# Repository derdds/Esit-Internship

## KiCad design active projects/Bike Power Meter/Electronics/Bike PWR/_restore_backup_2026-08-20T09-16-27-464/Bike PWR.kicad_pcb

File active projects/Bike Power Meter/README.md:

# Bike Power Meter

## Project Description
Add your project description here.

## Status
- Active/In Progress/Completed

## Key Files
- List important files here

## Notes
- Add any relevant notes

## Links
- Add links to documentation, repos, etc.

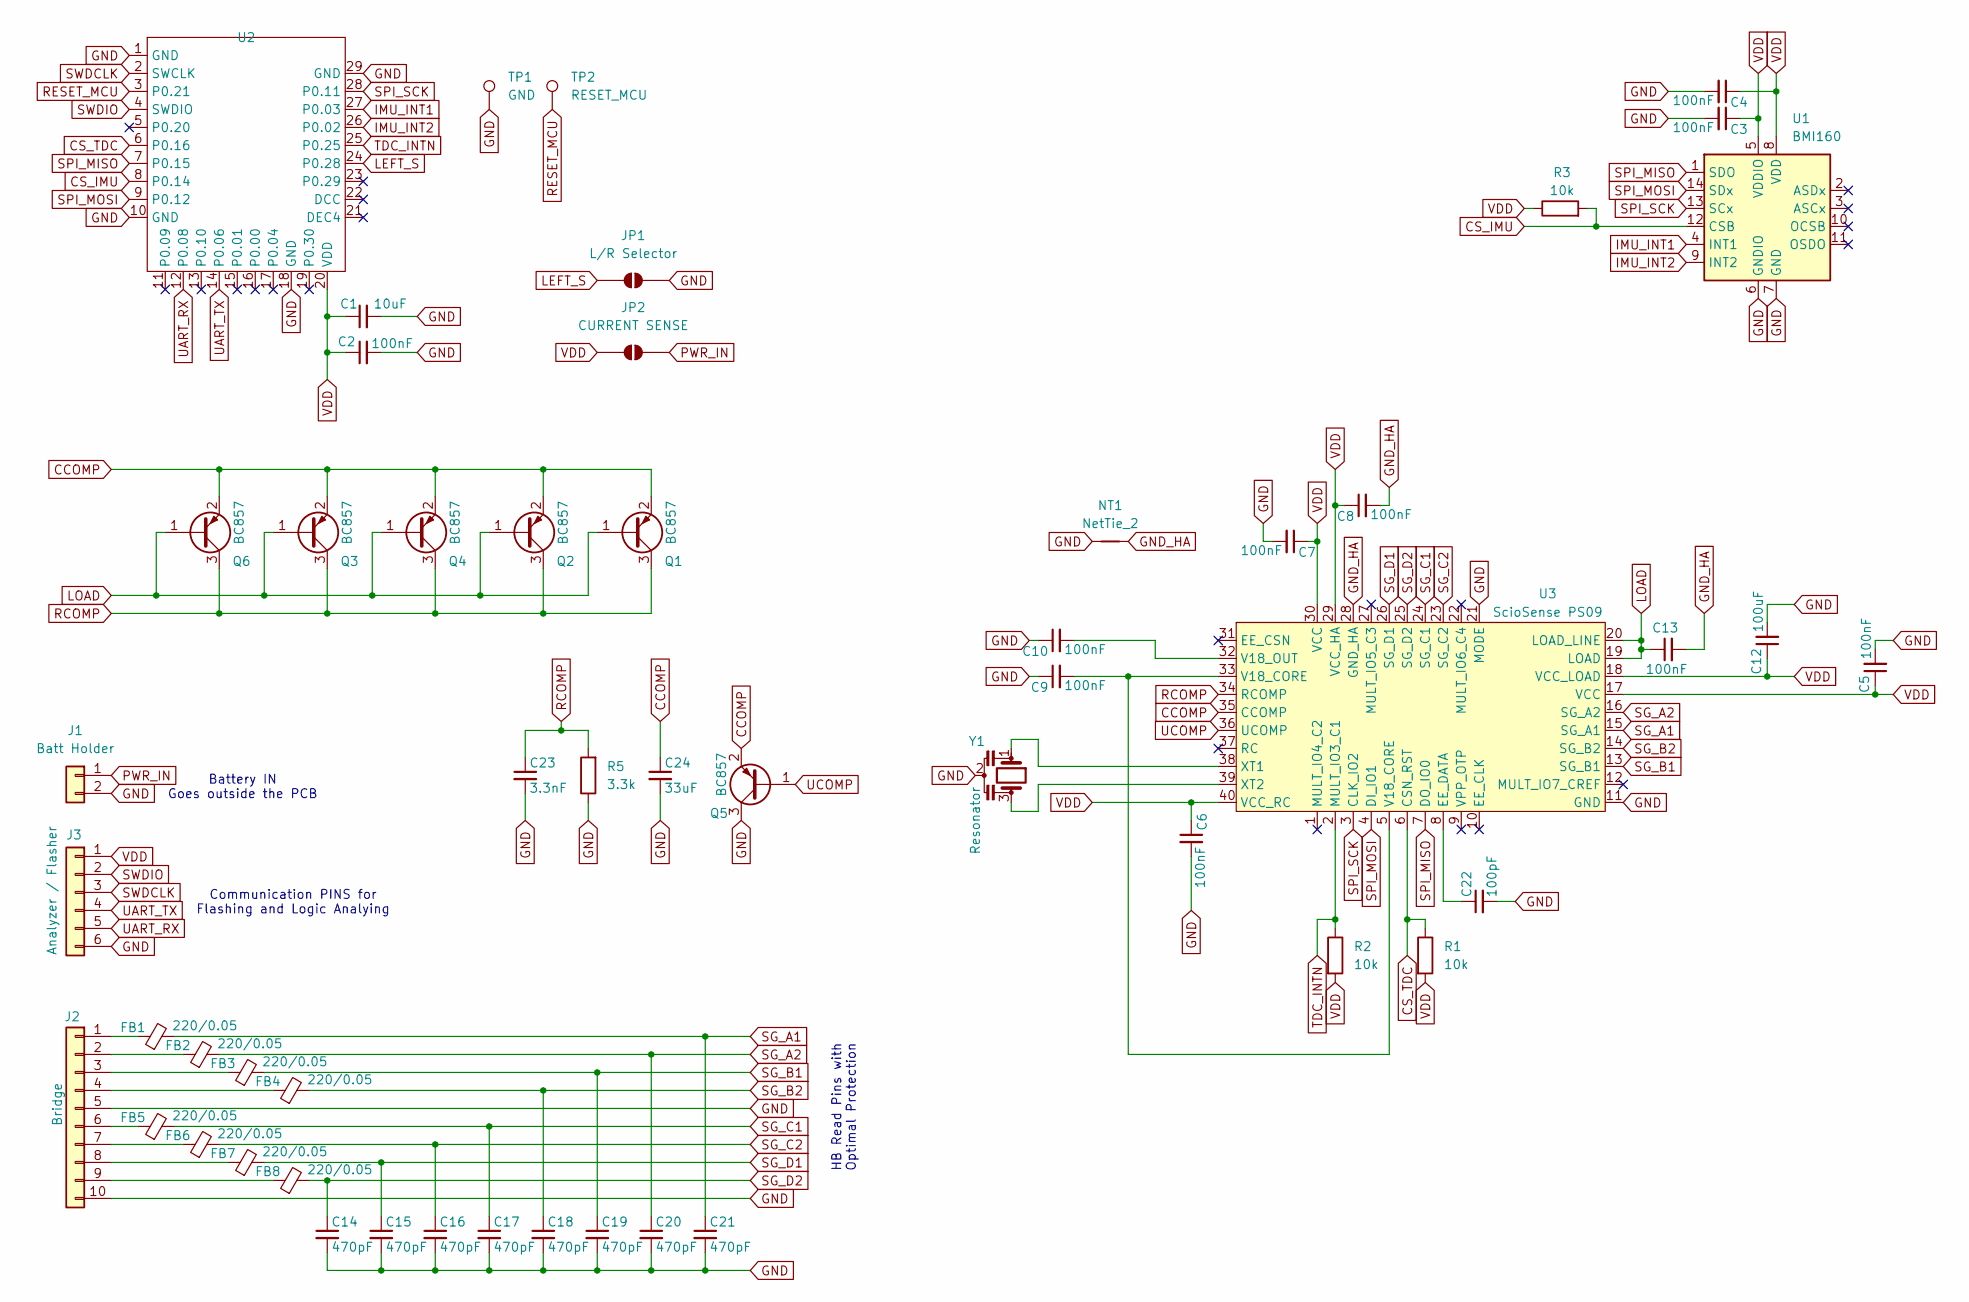
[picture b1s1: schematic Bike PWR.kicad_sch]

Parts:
C1: 10uF; C_0201_0603Metric_Pad0.64x0.40mm_HandSolder
C2, C3, C4, C5, C6, C7, C8, C9, C10, C13: 100nF; C_0201_0603Metric_Pad0.64x0.40mm_HandSolder
C12: 100uF; C_0201_0603Metric_Pad0.64x0.40mm_HandSolder
C14, C15, C16, C17, C18, C19, C20, C21: 470pF; C_0201_0603Metric_Pad0.64x0.40mm_HandSolder
C22: 100pF; C_0201_0603Metric_Pad0.64x0.40mm_HandSolder
C23: 3.3nF; C_0201_0603Metric_Pad0.64x0.40mm_HandSolder
C24: 33uF; C_0201_0603Metric_Pad0.64x0.40mm_HandSolder
FB1, FB2, FB3, FB4, FB5, FB6, FB7, FB8: 220/0.05; L_0201_0603Metric_Pad0.64x0.40mm_HandSolder
J1: Batt Holder; PWR Pins (2x2.54mm)
J2: Bridge; AFE SG (10x2.54mm)
J3: Analyzer / Flasher; UART Pins (6x2.54mm)
JP1: L/R Selector; SolderJumper-2_P1.3mm_Open_RoundedPad1.0x1.5mm
JP2: CURRENT SENSE; SolderJumper-2_P1.3mm_Open_RoundedPad1.0x1.5mm
NT1: NetTie_2; NetTie-2_SMD_Pad0.5mm
Q1, Q2, Q3, Q4, Q5, Q6: BC857; SOT-23
R1, R2, R3: 10k; R_0201_0603Metric_Pad0.64x0.40mm_HandSolder
R5: 3.3k; R_0201_0603Metric_Pad0.64x0.40mm_HandSolder
TP1: GND; TestPoint_Pad_D1.0mm
TP2: RESET_MCU; TestPoint_Pad_D1.0mm
U1: BMI160; Bosch_LGA-14_3x2.5mm_P0.5mm
U2: MDBT42V-512KV2
U3: ScioSense PS09; QFN-40-1EP_6x6mm_P0.5mm_EP4.6x4.6mm
Y1: Resonator; OSC_CSTCR4M00G53-R0

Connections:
CCOMP: C24.1, Q1.2 (E), Q2.2 (E), Q3.2 (E), Q4.2 (E), Q5.2 (E), Q6.2 (E), U3.35 (CCOMP)
CS_IMU: R3.2, U1.12 (CSB), U2.8 (P0.14)
CS_TDC: R1.1, U2.6 (P0.20), U3.6 (CSN_RST)
GND: C1.2, C2.2, C3.2, C4.2, C5.2, C6.2, C7.2, C9.1, C10.1, C12.2, C14.2, C15.2, C16.2, C17.2, C18.2, C19.2, C20.2, C21.2, C22.2, C23.2, C24.2, J1.2, J2.5, J2.10, J3.6, JP1.2 (B), NT1.1, Q5.3 (C), R5.1, TP1.1 (1_1), U1.6 (GNDIO), U1.7 (GND), U2.1 (GND), U2.10 (GND), U2.18 (GND), U2.29 (GND), U3.11 (GND), U3.21 (MODE), Y1.2; also elsewhere on the board
GND_HA: C8.2, C13.2, NT1.2, U3.28 (GND_HA)
IMU_INT1: U1.4 (INT1), U2.27 (P0.03)
IMU_INT2: U1.9 (INT2), U2.26 (P0.02)
LEFT_S: JP1.1 (A), U2.24 (P0.28); also elsewhere on the board
LOAD: C13.1, Q1.1 (B), Q2.1 (B), Q3.1 (B), Q4.1 (B), Q6.1 (B), U3.19 (LOAD), U3.20 (LOAD_LINE)
unnamed: C9.2, U3.5 (V18_CORE), U3.33 (V18_CORE)
unnamed: FB1.1, J2.1
unnamed: FB2.1, J2.2
unnamed: FB3.1, J2.3
unnamed: FB4.1, J2.4
unnamed: FB5.1, J2.6
unnamed: FB6.1, J2.7
unnamed: FB7.1, J2.8
unnamed: FB8.1, J2.9
unnamed: C22.1, U3.8 (EE_DATA)
unnamed: C10.2, U3.32 (V18_OUT)
unnamed: U3.38 (XT1), Y1.1
unnamed: U3.39 (XT2), Y1.3
PWR_IN: J1.1, JP2.2 (B); also elsewhere on the board
RCOMP: C23.1, Q1.3 (C), Q2.3 (C), Q3.3 (C), Q4.3 (C), Q6.3 (C), R5.2, U3.34 (RCOMP)
RESET_MCU: TP2.1 (1_1), U2.3 (P0.21)
SG_A1: C21.1, FB1.2, U3.15 (SG_A1)
SG_A2: C20.1, FB2.2, U3.16 (SG_A2)
SG_B1: C19.1, FB3.2, U3.13 (SG_B1)
SG_B2: C18.1, FB4.2, U3.14 (SG_B2)
SG_C1: C17.1, FB5.2, U3.24 (SG_C1)
SG_C2: C16.1, FB6.2, U3.23 (SG_C2)
SG_D1: C15.1, FB7.2, U3.26 (SG_D1)
SG_D2: C14.1, FB8.2, U3.25 (SG_D2)
SPI_MISO: U1.1 (SDO), U2.7 (P0.15), U3.7 (DO_IO0)
SPI_MOSI: U1.14 (SDx), U2.9 (P0.12), U3.4 (DI_IO1)
SPI_SCK: U1.13 (SCx), U2.28 (P0.11), U3.3 (CLK_IO2)
SWDCLK: J3.3, U2.2 (SWCLK)
SWDIO: J3.2, U2.4 (SWDIO)
TDC_INTN: R2.1, U2.25 (P0.25), U3.2 (MULT_IO3_C1)
UART_RX: J3.5, U2.12 (P0.08)
UART_TX: J3.4, U2.14 (P0.06)
UCOMP: Q5.1 (B), U3.36 (UCOMP)
VDD: C1.1, C2.1, C3.1, C4.1, C5.1, C6.1, C7.1, C8.1, C12.1, J3.1, JP2.1 (A), R1.2, R2.2, R3.1, U1.5 (VDDIO), U1.8 (VDD), U2.20 (VDD), U3.17 (VCC), U3.18 (VCC_LOAD), U3.29 (VCC_HA), U3.30 (VCC), U3.40 (VCC_RC); also elsewhere on the board

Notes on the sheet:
HB Read Pins with Optimal Protection
Communication PINS for Flashing and Logic Analying
Battery IN Goes outside the PCB

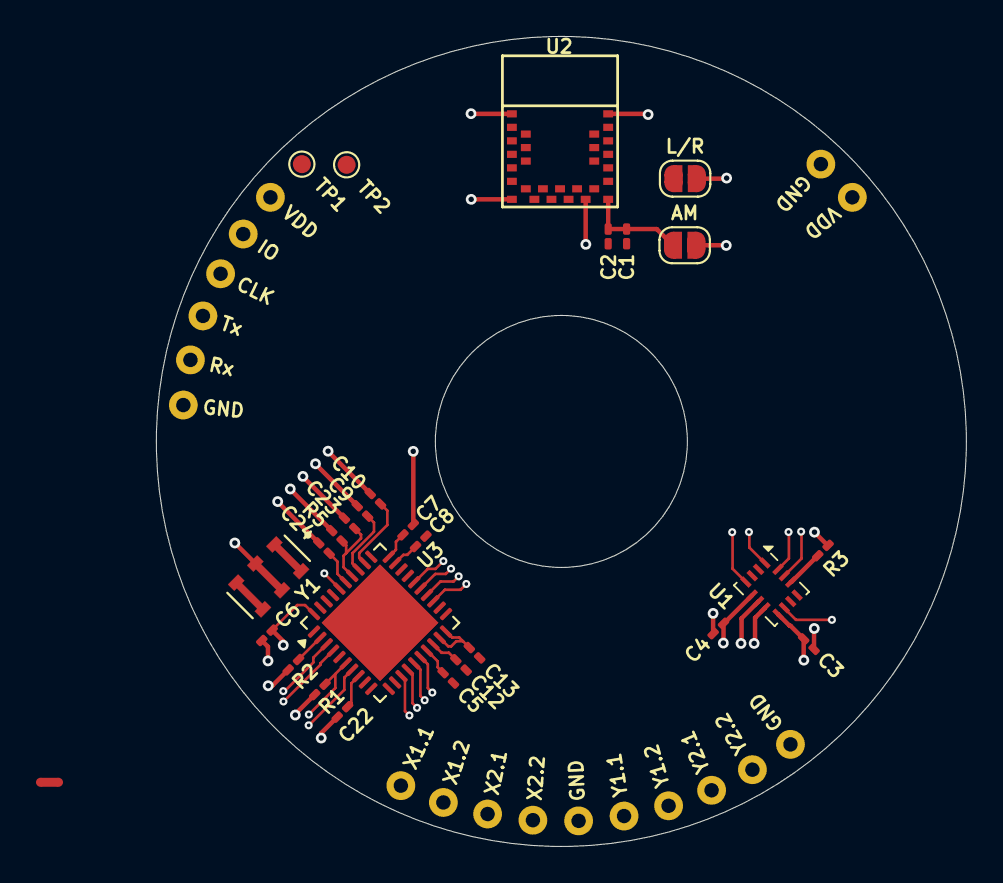
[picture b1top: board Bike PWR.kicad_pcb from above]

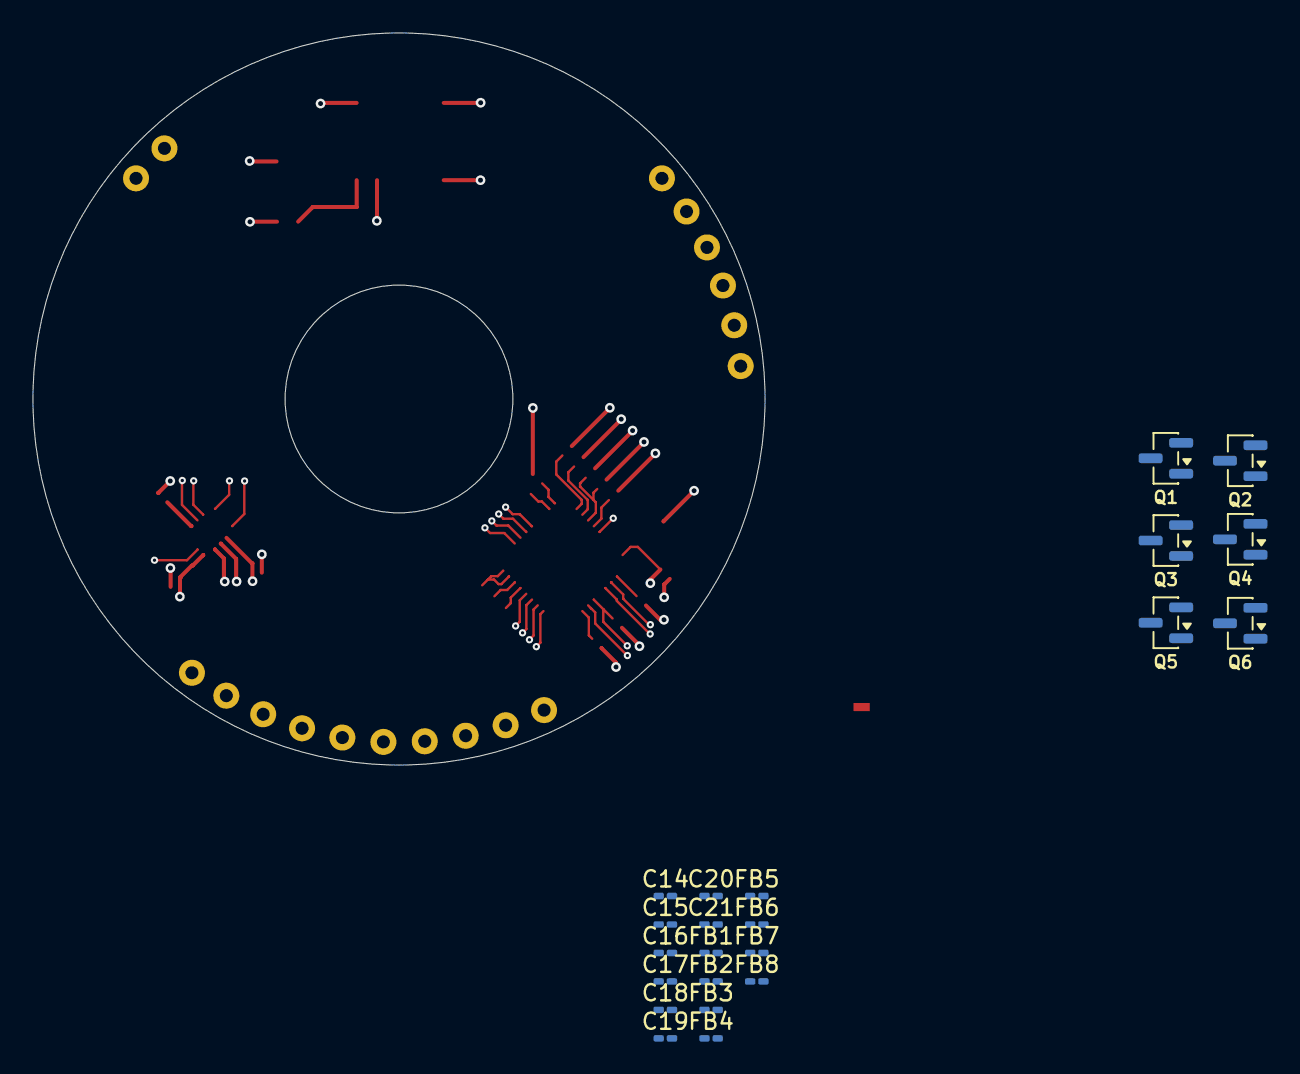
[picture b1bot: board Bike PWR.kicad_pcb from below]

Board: 4 copper layers, 45.0 x 45.0 mm, 53 parts (22 on the bottom side), 43 nets.

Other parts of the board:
AM: CURRENT SENSE; SolderJumper-2_P1.3mm_Open_RoundedPad1.0x1.5mm
L/R: L/R Selector; SolderJumper-2_P1.3mm_Open_RoundedPad1.0x1.5mm

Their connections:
GND: L/R.2 (B); also elsewhere on the board
LEFT_S: L/R.1 (A); also elsewhere on the board
PWR_IN: AM.2 (B); also elsewhere on the board
VDD: AM.1 (A); also elsewhere on the board

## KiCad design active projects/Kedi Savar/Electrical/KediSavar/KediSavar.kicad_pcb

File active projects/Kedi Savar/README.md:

# Kedi Savar

## Project Description
Add your project description here.

## Status
- Active/In Progress/Completed

## Key Files
- List important files here

## Notes
- Add any relevant notes

## Links
- Add links to documentation, repos, etc.

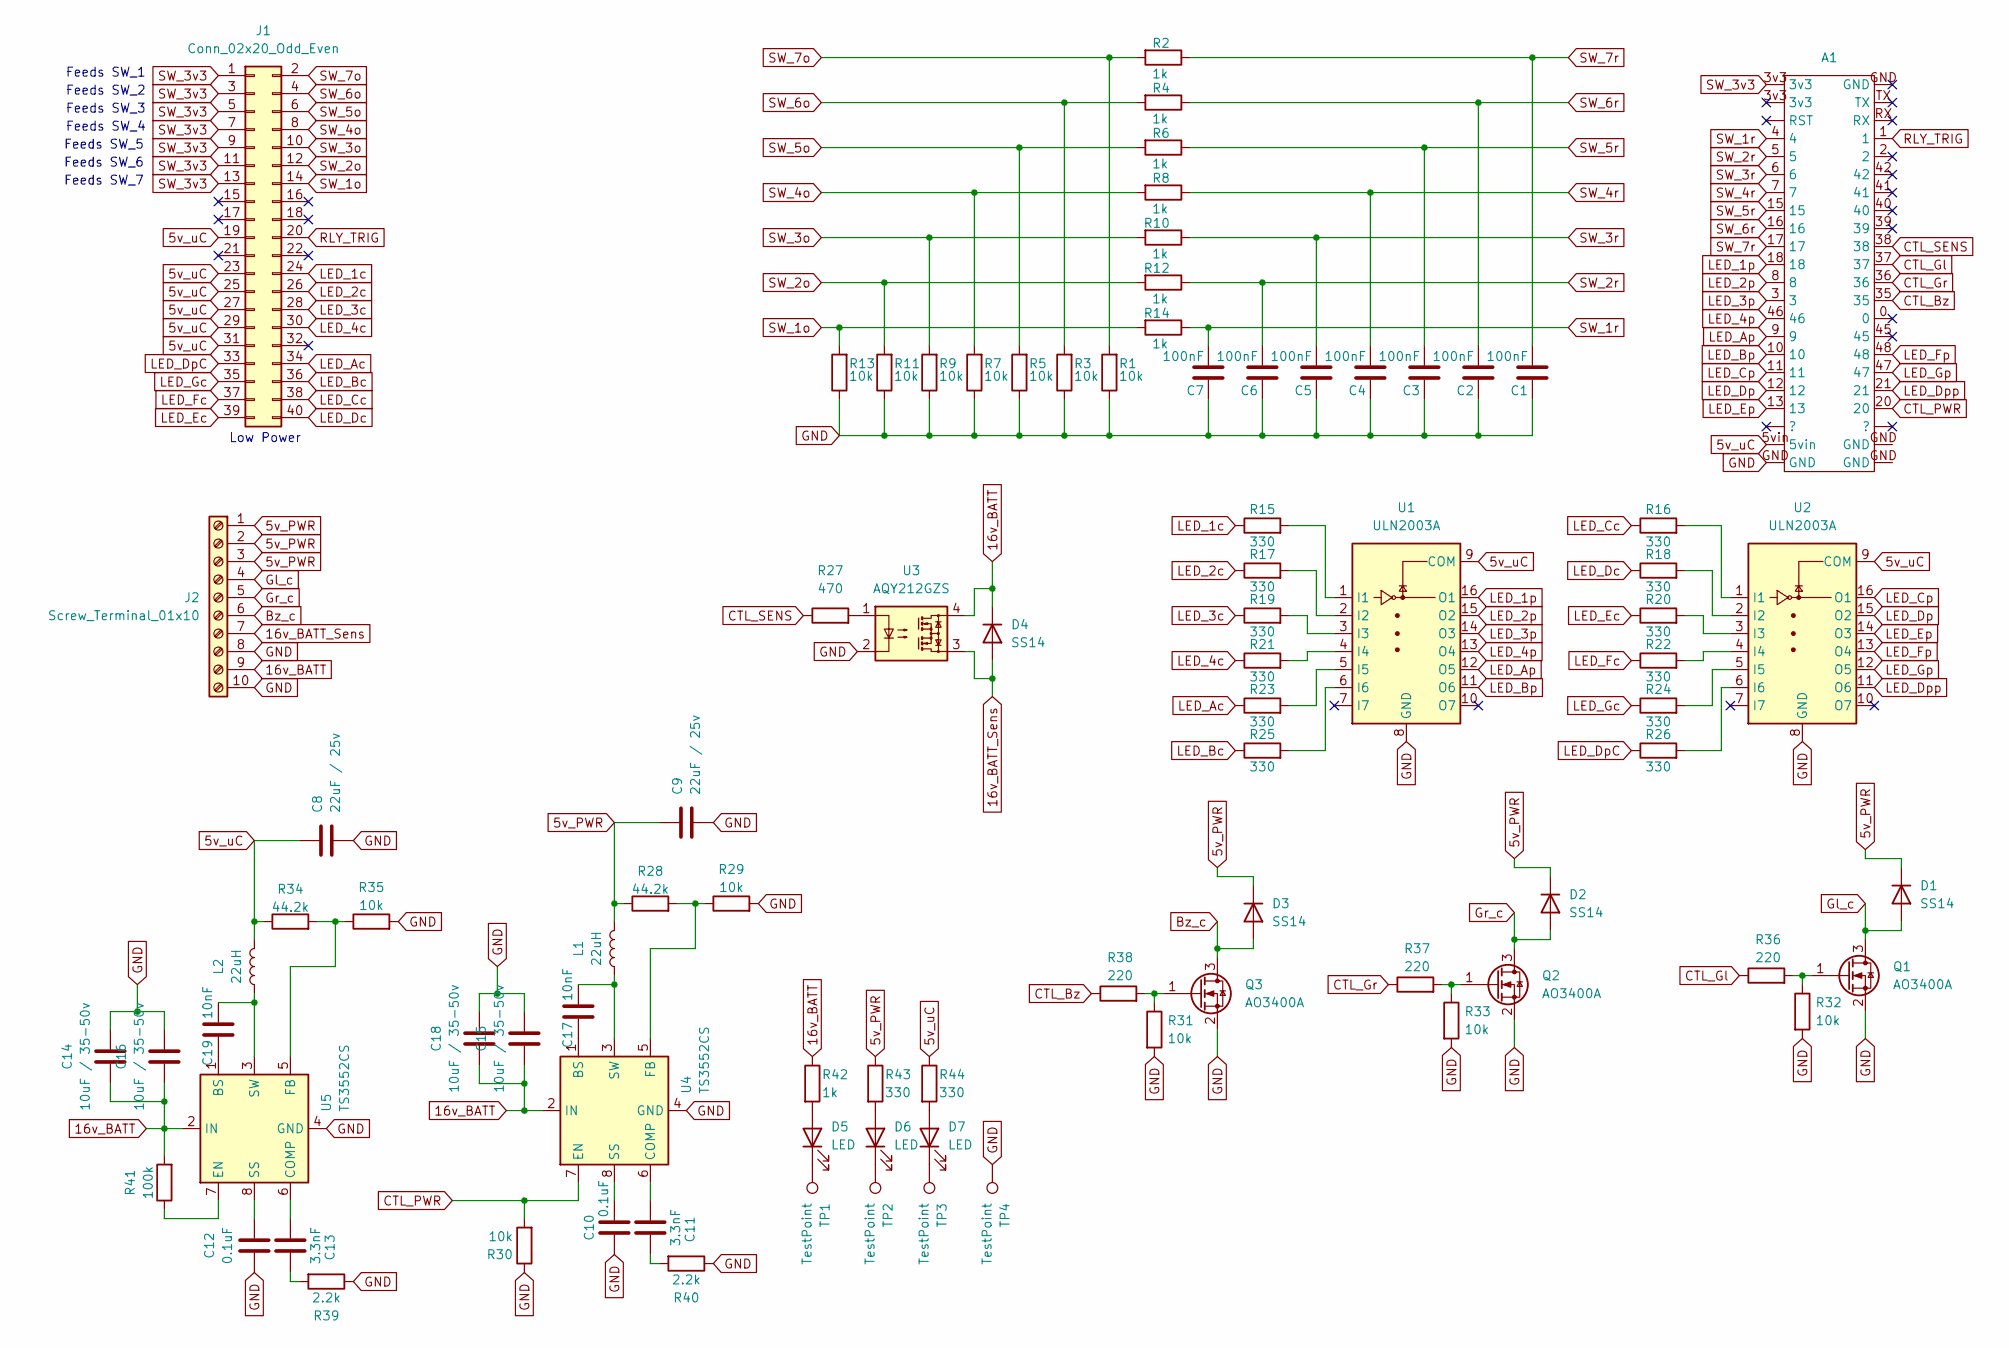
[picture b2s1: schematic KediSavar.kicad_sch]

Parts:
A1: ESP32 25.4mm
C1, C2, C3, C4, C5, C6, C7: 100nF; C_0805_2012Metric_Pad1.18x1.45mm_HandSolder
C8, C9: 22uF / 25v; C_1206_3216Metric_Pad1.33x1.80mm_HandSolder
C10, C12: 0.1uF; C_0805_2012Metric_Pad1.18x1.45mm_HandSolder
C11, C13: 3.3nF; C_0805_2012Metric_Pad1.18x1.45mm_HandSolder
C14, C15, C16, C18: 10uF / 35-50v; C_1206_3216Metric_Pad1.33x1.80mm_HandSolder
C17, C19: 10nF; C_0805_2012Metric_Pad1.18x1.45mm_HandSolder
D1, D2, D3, D4: SS14; D_3220_8050Metric_Pad2.65x5.15mm_HandSolder
D5, D6, D7: LED; LED_0805_2012Metric_Pad1.15x1.40mm_HandSolder
J1: Conn_02x20_Odd_Even; PinHeader_2x20_P2.54mm_Vertical
J2: Screw_Terminal_01x10; Wago 256 410
L1, L2: 22uH; L_12x12mm_H8mm
Q1, Q2, Q3: AO3400A; SOT-23
R1, R3, R5, R7, R9, R11, R13, R29, R30, R31, R32, R33, R35: 10k; R_0805_2012Metric_Pad1.20x1.40mm_HandSolder
R2, R4, R6, R8, R10, R12, R14, R42: 1k; R_0805_2012Metric_Pad1.20x1.40mm_HandSolder
R15, R16, R17, R18, R19, R20, R21, R22, R23, R24, R25, R26, R43, R44: 330; R_0805_2012Metric_Pad1.20x1.40mm_HandSolder
R27: 470; R_0805_2012Metric_Pad1.20x1.40mm_HandSolder
R28, R34: 44.2k; R_0805_2012Metric_Pad1.20x1.40mm_HandSolder
R36, R37, R38: 220; R_0805_2012Metric_Pad1.20x1.40mm_HandSolder
R39, R40: 2.2k; R_0805_2012Metric_Pad1.20x1.40mm_HandSolder
R41: 100k; R_0805_2012Metric_Pad1.20x1.40mm_HandSolder
TP1, TP2, TP3, TP4: TestPoint; TestPoint_Pad_1.5x1.5mm
U1, U2: ULN2003A; SOIC-16_3.9x9.9mm_P1.27mm
U3: AQY212GZS; SO-4_4.4x4.3mm_P2.54mm
U4, U5: TS3552CS; SOP-8_3.76x4.96mm_P1.27mm

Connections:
5v_PWR: C9.2, D1.1 (K), D2.1 (K), D3.1 (K), J2.1, J2.2, J2.3, L1.2, R28.1, R43.1
5v_uC: A1.5vin, C8.2, J1.19, J1.23, J1.25, J1.27, J1.29, J1.31, L2.2, R34.1, R44.1, U1.9 (COM), U2.9 (COM)
16v_BATT: C14.1, C15.1, C16.1, C18.1, D4.1 (K), J2.9, R41.2, R42.1, U3.4, U4.2 (IN), U5.2 (IN)
16v_BATT_Sens: D4.2 (A), J2.7, U3.3
Bz_c: D3.2 (A), J2.6, Q3.3 (D)
CTL_Bz: A1.35, R38.1
CTL_Gl: A1.37, R36.1
CTL_Gr: A1.36, R37.1
CTL_PWR: A1.20, R30.2, U4.7 (EN)
CTL_SENS: A1.38, R27.1
GND: A1.GND, C1.1, C2.1, C3.1, C4.1, C5.1, C6.1, C7.1, C8.1, C9.1, C10.1, C12.1, C14.2, C15.2, C16.2, C18.2, J2.8, J2.10, Q1.2 (S), Q2.2 (S), Q3.2 (S), R1.1, R3.1, R5.1, R7.1, R9.1, R11.1, R13.1, R29.2, R30.1, R31.2, R32.2, R33.2, R35.2, R39.1, R40.1, TP4.1, U1.8 (GND), U2.8 (GND), U3.2, U4.4 (GND), U5.4 (GND); also elsewhere on the board
Gl_c: D1.2 (A), J2.4, Q1.3 (D)
Gr_c: D2.2 (A), J2.5, Q2.3 (D)
LED_1c: J1.24, R15.1
LED_1p: A1.18, U1.16 (O1)
LED_2c: J1.26, R17.1
LED_2p: A1.8, U1.15 (O2)
LED_3c: J1.28, R19.1
LED_3p: A1.3, U1.14 (O3)
LED_4c: J1.30, R21.1
LED_4p: A1.46, U1.13 (O4)
LED_Ac: J1.34, R23.1
LED_Ap: A1.9, U1.12 (O5)
LED_Bc: J1.36, R25.1
LED_Bp: A1.10, U1.11 (O6)
LED_Cc: J1.38, R16.1
LED_Cp: A1.11, U2.16 (O1)
LED_Dc: J1.40, R18.1
LED_Dp: A1.12, U2.15 (O2)
LED_DpC: J1.33, R26.1
LED_Dpp: A1.21, U2.11 (O6)
LED_Ec: J1.39, R20.1
LED_Ep: A1.13, U2.14 (O3)
LED_Fc: J1.37, R22.1
LED_Fp: A1.48, U2.13 (O4)
LED_Gc: J1.35, R24.1
LED_Gp: A1.47, U2.12 (O5)
unnamed: C11.1, R40.2
unnamed: C13.1, R39.2
unnamed: D5.2 (A), R42.2
unnamed 40: D5.1 (K), TP1.1; also elsewhere on the board
unnamed: D6.2 (A), R43.2
unnamed 42: D6.1 (K), TP2.1; also elsewhere on the board
unnamed: D7.2 (A), R44.2
unnamed 44: D7.1 (K), TP3.1; also elsewhere on the board
unnamed: Q1.1 (G), R32.1, R36.2
unnamed: Q2.1 (G), R33.1, R37.2
unnamed: Q3.1 (G), R31.1, R38.2
unnamed: R27.2, U3.1
unnamed: R15.2, U1.1 (I1)
unnamed: R17.2, U1.2 (I2)
unnamed: R19.2, U1.3 (I3)
unnamed: R21.2, U1.4 (I4)
unnamed: R23.2, U1.5 (I5)
unnamed: R25.2, U1.6 (I6)
unnamed: R16.2, U2.1 (I1)
unnamed: R18.2, U2.2 (I2)
unnamed: R20.2, U2.3 (I3)
unnamed: R22.2, U2.4 (I4)
unnamed: R24.2, U2.5 (I5)
unnamed: R26.2, U2.6 (I6)
unnamed: C17.1, U4.1 (BS)
unnamed: C11.2, U4.6 (COMP)
unnamed: R28.2, R29.1, U4.5 (FB)
unnamed: C10.2, U4.8 (SS)
unnamed: C17.2, L1.1, U4.3 (SW)
unnamed: C19.1, U5.1 (BS)
unnamed: C13.2, U5.6 (COMP)
unnamed: R41.1, U5.7 (EN)
unnamed: R34.2, R35.1, U5.5 (FB)
unnamed: C12.2, U5.8 (SS)
unnamed: C19.2, L2.1, U5.3 (SW)
RLY_TRIG: A1.1, J1.20
SW_1o: J1.14, R13.2, R14.2
SW_1r: A1.4, C7.2, R14.1
SW_2o: J1.12, R11.2, R12.2
SW_2r: A1.5, C6.2, R12.1
SW_3o: J1.10, R9.2, R10.2
SW_3r: A1.6, C5.2, R10.1
SW_3v3: A1.3v3, J1.1, J1.3, J1.5, J1.7, J1.9, J1.11, J1.13
SW_4o: J1.8, R7.2, R8.2
SW_4r: A1.7, C4.2, R8.1
SW_5o: J1.6, R5.2, R6.2
SW_5r: A1.15, C3.2, R6.1
SW_6o: J1.4, R3.2, R4.2
SW_6r: A1.16, C2.2, R4.1
SW_7o: J1.2, R1.2, R2.2
SW_7r: A1.17, C1.2, R2.1

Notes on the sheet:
Feeds SW_3
Feeds SW_1
Feeds SW_6
Feeds SW_4
Feeds SW_7
Feeds SW_2
Low Power
Feeds SW_5

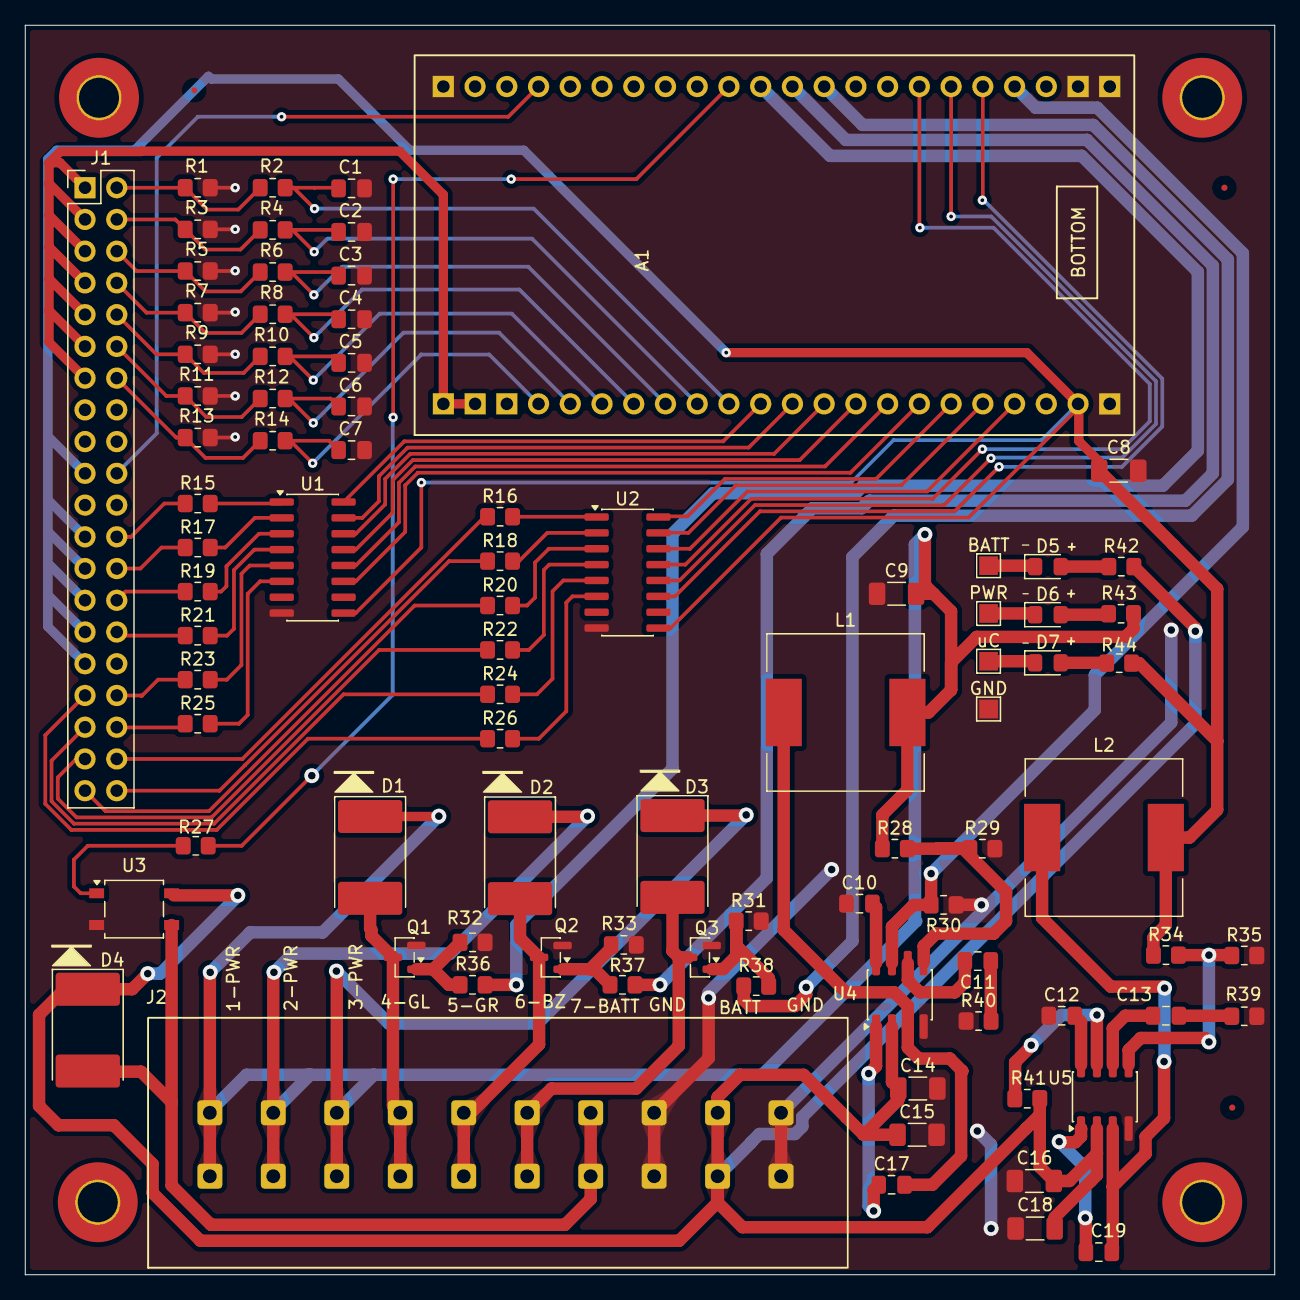
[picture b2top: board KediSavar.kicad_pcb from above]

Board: 2 copper layers, 100.0 x 100.0 mm, 87 parts (0 on the bottom side), 88 nets.

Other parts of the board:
BATT: TestPoint; TestPoint_Pad_1.5x1.5mm
GND: TestPoint; TestPoint_Pad_1.5x1.5mm
PWR: TestPoint; TestPoint_Pad_1.5x1.5mm
uC: TestPoint; TestPoint_Pad_1.5x1.5mm

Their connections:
GND: GND.1 (1_1); also elsewhere on the board
unnamed 40: BATT.1 (1_1); also elsewhere on the board
unnamed 42: PWR.1 (1_1); also elsewhere on the board
unnamed 44: uC.1 (1_1); also elsewhere on the board

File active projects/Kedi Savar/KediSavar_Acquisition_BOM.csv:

Quantity,Target Part,Original Value,References,Summary,Link
1,2x 1x22 Female Pin Header,,A1,2 pieces of 1x22 female 2.54mm pitch connectors,https://www.we-online.com/en/components/products/PHD_2_54_TH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
2,CORE MASTER SRI1004-220M,22uH,"L1, L2",INDUCTOR POWER 22UH 10X10MM SMD 3A,https://www.ozdisan.com/en/p/fixed-inductors-468/core-master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
4,Generic SMD Test Point,TestPoint,"TP1, TP2, TP3, TP4",Test Point Pad 1.5x1.5mm,
3,HOTTECH AO3406-HT,AO3400A,"Q1, Q2, Q3",MOSFET 3.6A 30V N-CH SOT23 TRENCH SMT,https://electroist.com/tr-tr/product/12971/ao3406-ht
3,INFOREC LED XC-0805YVC,LED,"D5, D6, D7",LED SMD 0805 YELLOW 100mcd 120° WATER CLEAR,https://www.ozdisan.com/en/p/led-signal-color-361/inforec-le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
1,Panasonic AQY212GSZ,AQY212GZS,U3,PhotoMOS Relay SOP-4,https://industry.panasonic.eu/components/relays/photomos-rel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
2,SAMSUNG CL21B103KBANNNC,10nF,"C17, C19",MLCC 0805 10nF 50V 10% X7R,https://product.samsungsemiconductors.com/mlcc/CL21B103KBANNNC.do
2,SAMSUNG CL21B104KBCNNNC,0.1uF,"C10, C12",MLCC 0805 100nF (0.1uF) 50V 10% X7R,https://product.samsungsemiconductors.com/mlcc/CL21B104KBCNNNC.do
7,SAMSUNG CL21B104KBCNNNC,100nF,"C1, C2, C3, C4, C5, C6, C7",MLCC 0805 100nF 50V 10% X7R,https://product.samsungsemiconductors.com/mlcc/CL21B104KBCNNNC.do
2,SAMSUNG CL21B332KBANNNC,3.3nF,"C11, C13",MLCC 0805 3.3nF 50V 10% X7R,https://product.samsungsemiconductors.com/mlcc/CL21B332KBANNNC.do
4,SAMSUNG CL31B106KBHNNNE,10uF / 35-50v,"C14, C15, C16, C18",MLCC 1206 10uF 50V 10% X7R,https://product.samsungsemiconductors.com/mlcc/CL31B106KBHNNNE.do
2,SAMSUNG CL32B226KAJNNNE,22uF / 25v,"C8, C9",MLCC 1210 22uF 25V 10% X7R,https://product.samsungsemiconductors.com/mlcc/CL32B226KAJNNNE.do
2,STMicroelectronics ULN2003A,ULN2003A,"U1, U2",IC-2003 PWR RELAY 7NPN 1:1 16DIP/SOIC,https://www.st.com/en/interfaces-and-transceivers/uln2003a.html
4,TAIWAN SEMICONDUCTOR SS14,SS14,"D1, D2, D3, D4",DIODE SCHOTTKY 40V 1A DO214AC (SMA),https://www.taiwansemi.com/en/products/details/SS14
2,TAIWAN SEMICONDUCTOR TS3552CS RLG,TS3552CS,"U4, U5",IC DC-DC CONVERTER SMD 2A/350kHz TS3552 SOP8,https://www.taiwansemi.com/en/products/details/TS3552CS
1,WAGO 256-410,Screw_Terminal_01x10,J2,PCB Terminal Block 10-Pole 2.5mm2 256 Series,https://www.wago.com/global/pcb-terminal-blocks-and-connecto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
1,WURTH ELEKTRONIK 61304021121,Conn_02x20_Odd_Even,J1,PIN HEADER 40PIN (2x20) 2.54mm,https://www.we-online.com/en/components/products/PHD_2_54_SM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
1,YAGEO RC0805FR-07100KL,100k,R41,RES 0805 100K Ohms 1% 1/8W,https://www.yageo.com/en/Product/Index/Resistors/rc_series
13,YAGEO RC0805FR-0710KL,10k,"R1, R11, R13, R29, R3, R30, R31, R32, R33, R35, R5, R7, R9",RES 0805 10K Ohms 1% 1/8W,https://www.yageo.com/en/Product/Index/Resistors/rc_series
8,YAGEO RC0805FR-071KL,1k,"R10, R12, R14, R2, R4, R42, R6, R8",RES 0805 1K Ohms 1% 1/8W,https://www.yageo.com/en/Product/Index/Resistors/rc_series
3,YAGEO RC0805FR-07220RL,220,"R36, R37, R38",RES 0805 220 Ohms 1% 1/8W,https://www.yageo.com/en/Product/Index/Resistors/rc_series
2,https://www.ozdisan.com/p/smt-smd-ve-cip-direncler-194/yageo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,2.2k,"R39, R40",RES 0805 2.2K Ohms 1% 1/8W,https://www.yageo.com/en/Product/Index/Resistors/rc_series
14,YAGEO RC0805FR-07330RL,330,"R15, R16, R17, R18, R19, R20, R21, R22, R23, R24, R25, R26, R43, R44",RES 0805 330 Ohms 1% 1/8W,https://www.yageo.com/en/Product/Index/Resistors/rc_series
2,YAGEO RC0805FR-0744K2L,44.2k,"R28, R34",RES 0805 44.2K Ohms 1% 1/8W,https://www.yageo.com/en/Product/Index/Resistors/rc_series
1,YAGEO RC0805FR-07470RL,470,R27,RES 0805 470 Ohms 1% 1/8W,https://www.yageo.com/en/Product/Index/Resistors/rc_series

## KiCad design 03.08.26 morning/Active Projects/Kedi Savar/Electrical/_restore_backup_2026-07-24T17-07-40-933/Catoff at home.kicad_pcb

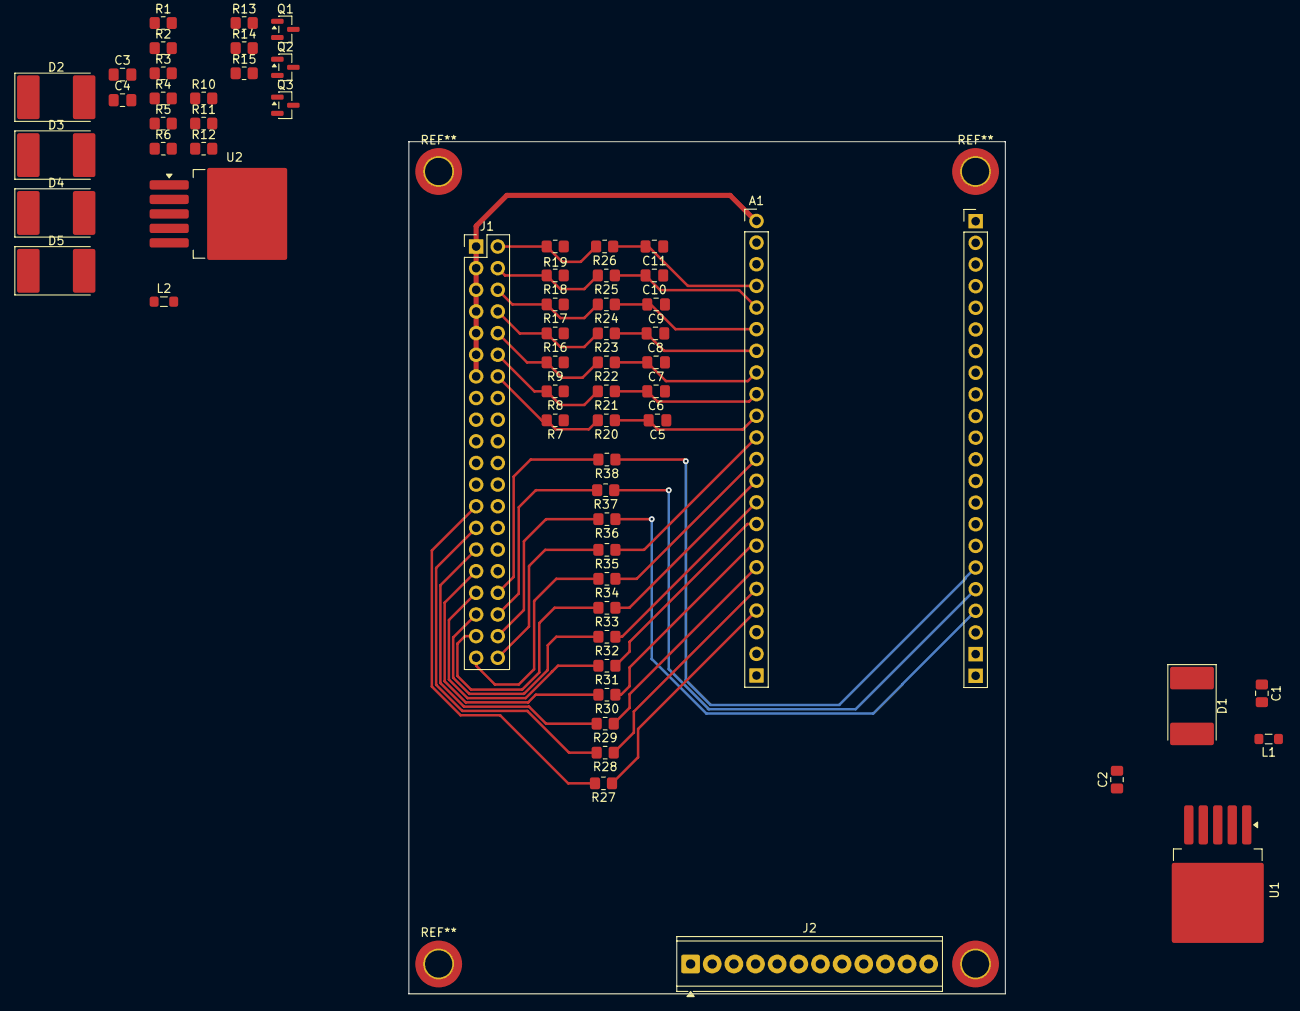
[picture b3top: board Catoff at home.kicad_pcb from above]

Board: 2 copper layers, 70.0 x 100.0 mm, 64 parts (0 on the bottom side), 55 nets.

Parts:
A1: esp32 placeholder 25.7
C1, C2, C3, C4: C; C_0805_2012Metric_Pad1.18x1.45mm_HandSolder
C5, C6, C7, C8, C9, C10, C11: 100nF; C_0805_2012Metric_Pad1.18x1.45mm_HandSolder
D1, D2: D_Schottky; D_3220_8050Metric_Pad2.65x5.15mm_HandSolder
D3, D4, D5: D; D_3220_8050Metric_Pad2.65x5.15mm_HandSolder
J1: Conn_02x20_Odd_Even; PinHeader_2x20_P2.54mm_Vertical
J2: Screw_Terminal_01x12; TerminalBlock_Phoenix_MPT-0,5-12-2.54_1x12_P2.54mm_Horizont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
L1, L2: L; L_0805_2012Metric_Pad1.05x1.20mm_HandSolder
Q1, Q2, Q3: AOD454A; SOT-23
R1, R2, R3, R4, R5, R6, R10, R11, R12, R13, R14, R15: R; R_0805_2012Metric_Pad1.20x1.40mm_HandSolder
R7, R8, R9, R16, R17, R18, R19: 10k; R_0805_2012Metric_Pad1.20x1.40mm_HandSolder
R20, R21, R22, R23, R24, R25, R26: 100; R_0805_2012Metric_Pad1.20x1.40mm_HandSolder
R27, R28, R29, R30, R31, R32, R33, R34, R35, R36, R37, R38: 330; R_0805_2012Metric_Pad1.20x1.40mm_HandSolder
U1, U2: LM2596S-5; TO-263-5_TabPin3

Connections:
/5v_PWR: C4.1, D3.1 (K), D4.1 (K), D5.1 (K), J2.1, J2.2, J2.3, L2.2, U2.4 (FB)
/5v_uC: A1.5vin, C1.1, L1.2, U1.4 (FB)
/16v_BATT: C2.1, C3.1, J2.10, J2.11, U1.1 (VIN), U2.1 (VIN)
/Bz_c: D5.2 (A), J2.6, Q3.3 (D)
/CTL_PWR: A1.48, U2.5 (~ON/OFF)
/Gl_c: D4.2 (A), J2.5, Q2.3 (D)
/Gr_c: D3.2 (A), J2.4, Q1.3 (D)
/LED_1a: J1.25, R27.2
/LED_1p: A1.13, R27.1
/LED_2a: J1.27, R28.2
/LED_2p: A1.12, R28.1
/LED_3a: J1.29, R29.2
/LED_3p: A1.11, R29.1
/LED_4a: J1.31, R30.2
/LED_4p: A1.10, R30.1
/LED_Aa: J1.33, R31.2
/LED_Ap: A1.9, R31.1
/LED_Ba: J1.35, R32.2
/LED_Bp: A1.46, R32.1
/LED_Ca: J1.37, R33.2
/LED_Cp: A1.3, R33.1
/LED_Da: J1.39, R34.2
/LED_Dp: A1.8, R34.1
/LED_Dpa: J1.34, R38.2
/LED_Dpp: A1.47, R38.1
/LED_Ea: J1.40, R35.2
/LED_Ep: A1.18, R35.1
/LED_Fa: J1.38, R36.2
/LED_Fp: A1.20, R36.1
/LED_Ga: J1.36, R37.2
/LED_Gp: A1.21, R37.1
/SW_1i: R1.2, R4.1
/SW_1o: J1.14, R4.2, R7.2, R20.2
/SW_1r: A1.17, C5.2, R20.1
/SW_2i: R2.2, R5.2
/SW_2o: J1.12, R5.1, R8.2, R21.2
/SW_2r: A1.16, C6.2, R21.1
/SW_3i: R3.2, R6.2
/SW_3o: J1.10, R6.1, R9.2, R22.2
/SW_3r: A1.15, C7.2, R22.1
/SW_3v3: A1.3v3, J1.1, J1.3, J1.5, J1.7, J1.9, J1.11, J1.13
/SW_4o: J1.8, R16.2, R23.2
/SW_4r: A1.7, C8.2, R23.1
/SW_5o: J1.6, R17.2, R24.2
/SW_5r: A1.6, C9.2, R24.1
/SW_6o: J1.4, R18.2, R25.2
/SW_6r: A1.5, C10.2, R25.1
/SW_7o: J1.2, R19.2, R26.2
/SW_7r: A1.4, C11.2, R26.1
GND: A1.GND, C1.2, C2.2, C3.2, C4.2, C5.1, C6.1, C7.1, C8.1, C9.1, C10.1, C11.1, D1.2 (A), D2.2 (A), J1.24, J1.26, J1.28, J1.30, J1.32, J2.12, Q1.2 (S), Q2.2 (S), Q3.2 (S), R1.1, R2.1, R3.1, R7.1, R8.1, R9.1, R10.2, R13.2, R15.2, R16.1, R17.1, R18.1, R19.1, U1.3 (GND), U1.5 (~ON/OFF), U2.3 (GND)
unnamed: D1.1 (K), L1.1, U1.2 (OUT)
unnamed: D2.1 (K), L2.1, U2.2 (OUT)
unnamed: Q1.1 (G), R10.1, R11.2
unnamed: Q2.1 (G), R12.2, R13.1
unnamed: Q3.1 (G), R14.2, R15.1

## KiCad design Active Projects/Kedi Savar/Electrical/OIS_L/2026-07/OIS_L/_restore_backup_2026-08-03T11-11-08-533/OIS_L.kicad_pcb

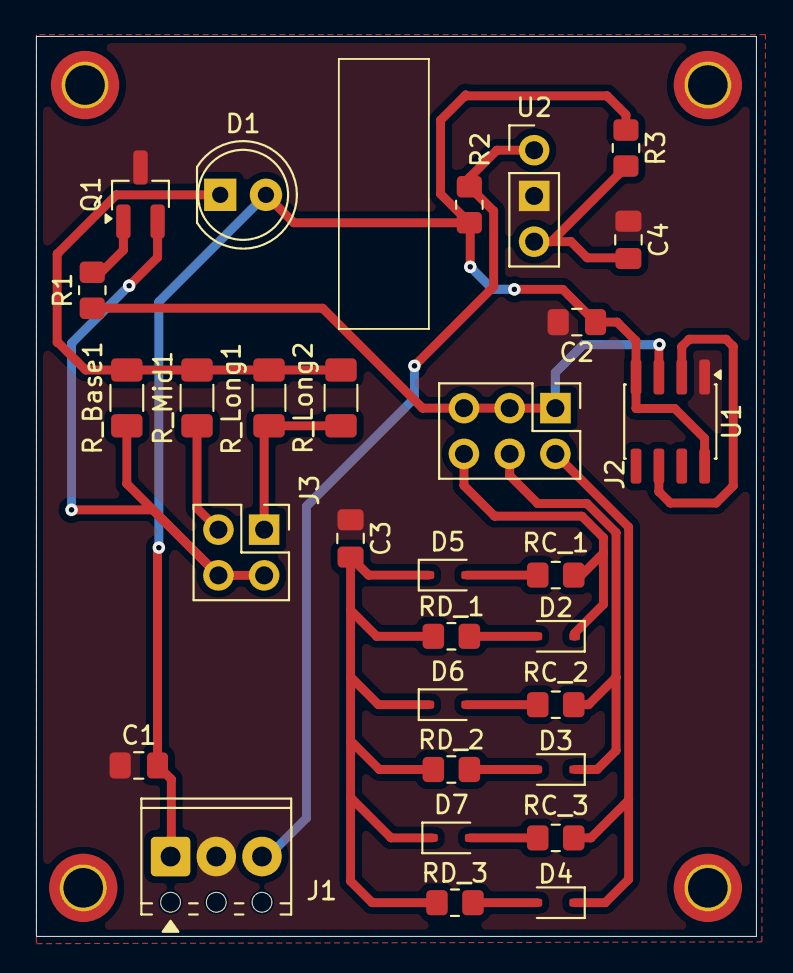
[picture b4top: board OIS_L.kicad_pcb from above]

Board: 2 copper layers, 40.0 x 50.0 mm, 30 parts (0 on the bottom side), 21 nets.

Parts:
C1: 10uF; C_0805_2012Metric_Pad1.18x1.45mm_HandSolder
C2, C4: 100 nF; C_0805_2012Metric_Pad1.18x1.45mm_HandSolder
C3: 1nF; C_0805_2012Metric_Pad1.18x1.45mm_HandSolder
D1: TSAL6100; LED_D5.0mm
D2, D3, D4, D5, D6, D7: 1N4148WS; D_SOD-323
J1: Screw_Terminal_01x03; TerminalBlock_Phoenix_MPT-0,5-3-2.54_1x03_P2.54mm_Horizontal
J2: Conn_02x03_Odd_Even; PinHeader_2x03_P2.54mm_Vertical
J3: Conn_02x02_Odd_Even; PinHeader_2x02_P2.54mm_Vertical
Q1: SI2308BDS-T1-GE3; SOT-23_Handsoldering
R1, R3: 100; R_0805_2012Metric_Pad1.20x1.40mm_HandSolder
R2: 10k; R_0805_2012Metric_Pad1.20x1.40mm_HandSolder
RC_1: 1.82k; R_0805_2012Metric_Pad1.20x1.40mm_HandSolder
RC_2: 3.65k; R_0805_2012Metric_Pad1.20x1.40mm_HandSolder
RC_3: 9.31k; R_0805_2012Metric_Pad1.20x1.40mm_HandSolder
RD_1: 35.7k; R_0805_2012Metric_Pad1.20x1.40mm_HandSolder
RD_2: 34k; R_0805_2012Metric_Pad1.20x1.40mm_HandSolder
RD_3: 28k; R_0805_2012Metric_Pad1.20x1.40mm_HandSolder
R_Base1: 68; R_1206_3216Metric_Pad1.30x1.75mm_HandSolder
R_Long1, R_Long2: 36; R_1206_3216Metric_Pad1.30x1.75mm_HandSolder
R_Mid1: 33; R_1206_3216Metric_Pad1.30x1.75mm_HandSolder
U1: LMC555xM; SOIC-8_3.9x4.9mm_P1.27mm
U2: TSSP4038; TSSP-4038

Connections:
5v_SYS: C1.2, C2.1, D1.2 (A), J1.1, R2.1, R3.1, U1.4 (~RST), U1.8 (VCC)
GND: C1.1, C2.2, C3.1, C4.1, J1.2, Q1.3 (S), U1.1 (GND), U2.2 (GND)
unnamed: D1.1 (K), R_Base1.2, R_Long1.2, R_Long2.2, R_Mid1.2
unnamed: D2.2 (A), RD_1.2
unnamed: D2.1 (K), J2.6, RC_1.1
unnamed: D3.2 (A), RD_2.2
unnamed: D3.1 (K), J2.4, RC_2.1
unnamed: D4.2 (A), RD_3.2
unnamed: D4.1 (K), J2.2, RC_3.1
unnamed: D5.2 (A), RC_1.2
unnamed: C3.2, D5.1 (K), D6.1 (K), D7.1 (K), RD_1.1, RD_2.1, RD_3.1
unnamed: D6.2 (A), RC_2.2
unnamed: D7.2 (A), RC_3.2
unnamed: J3.1, R_Long1.1, R_Long2.1
unnamed: J3.2, J3.4, Q1.2 (D), R_Base1.1
unnamed: J3.3, R_Mid1.1
unnamed: Q1.1 (G), R1.2
unnamed: U1.2 (TRIG), U1.6 (THRES)
unnamed: C4.2, R3.2, U2.3 (Vcc)
OUT: J1.3, R2.2, U2.1 (OUT)
Signal: J2.1, J2.3, J2.5, R1.1, U1.3 (OUT)
